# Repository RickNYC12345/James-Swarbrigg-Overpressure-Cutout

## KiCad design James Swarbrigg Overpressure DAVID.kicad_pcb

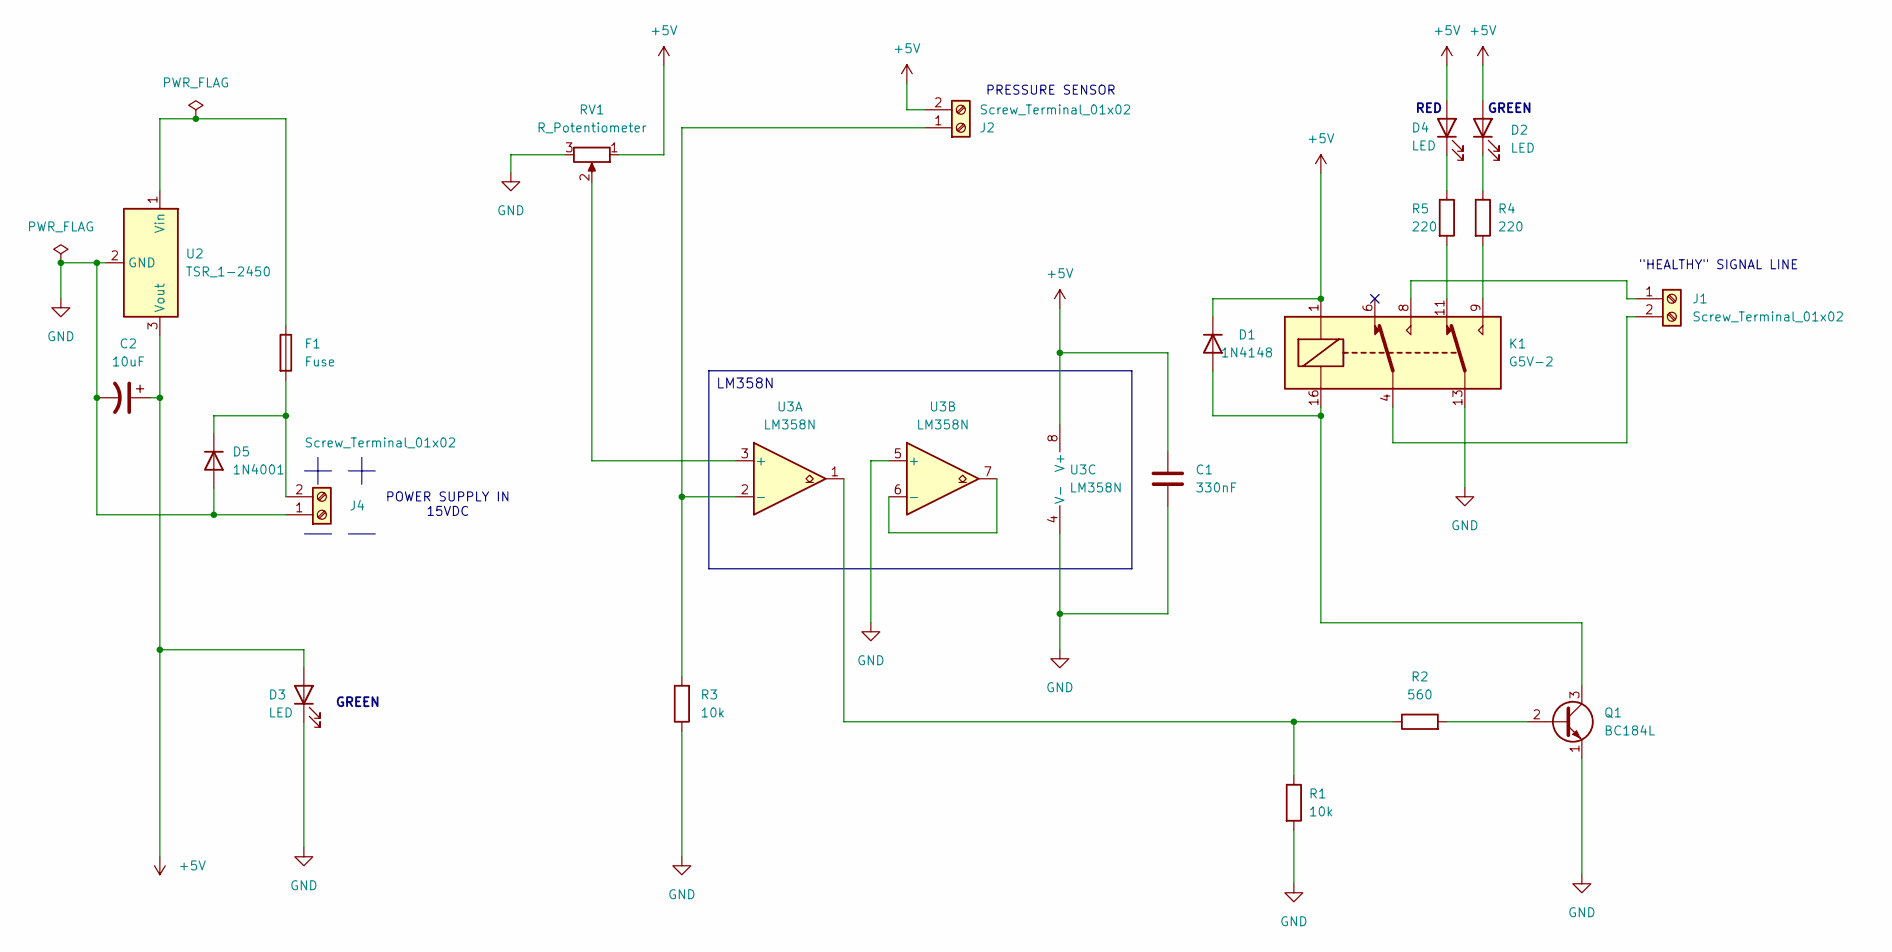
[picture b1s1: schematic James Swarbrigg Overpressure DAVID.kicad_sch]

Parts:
C1: 330nF; C_Rect_L7.2mm_W3.5mm_P5.00mm_FKS2_FKP2_MKS2_MKP2
C2: 10uF; CP_Radial_D5.0mm_P2.00mm
D1: 1N4148; D_DO-35_SOD27_P7.62mm_Horizontal
D2, D3, D4: LED; LED_D5.0mm
D5: 1N4001; D_DO-41_SOD81_P10.16mm_Horizontal
F1: Fuse; Fuseholder_Clip-5x20mm_Eaton_1A5601-01_Inline_P20.80x6.76mm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
J1, J2, J4: Screw_Terminal_01x02; TerminalBlock_Phoenix_MPT-0,5-2-2.54_1x02_P2.54mm_Horizontal
K1: G5V-2; Relay_DPDT_Omron_G5V-2
Q1: BC184L; TO-92_Inline
R1, R3: 10k; R_Axial_DIN0207_L6.3mm_D2.5mm_P10.16mm_Horizontal
R2: 560; R_Axial_DIN0207_L6.3mm_D2.5mm_P10.16mm_Horizontal
R4, R5: 220; R_Axial_DIN0207_L6.3mm_D2.5mm_P10.16mm_Horizontal
RV1: R_Potentiometer; Potentiometer_Bourns_3299P_Horizontal
U2: TSR_1-2450; Converter_DCDC_TRACO_TSR-1_THT
U3: LM358N; DIP-8_W7.62mm

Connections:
+5V: C1.1, C2.1, D1.1 (K), D2.2 (A), D3.2 (A), D4.2 (A), J2.2, K1.1, RV1.1, U2.3 (Vout), U3.8 (V+)
GND: C1.2, C2.2, D3.1 (K), D5.2 (A), J4.1, K1.13, Q1.1 (E), R1.2, R3.1, RV1.3, U2.2 (GND), U3.4 (V-), U3.5 (+)
unnamed: D1.2 (A), K1.16, Q1.3 (C)
unnamed: D2.1 (K), R4.1
unnamed: D4.1 (K), R5.1
unnamed: D5.1 (K), F1.2, J4.2
unnamed: J1.1, K1.8
unnamed: J1.2, K1.4
unnamed: J2.1, R3.2, U3.2 (-)
unnamed: K1.9, R4.2
unnamed: K1.11, R5.2
unnamed: Q1.2 (B), R2.2
unnamed: R1.1, R2.1, U3.1
unnamed: F1.1, U2.1 (Vin)
unnamed: RV1.2, U3.3 (+)
unnamed: U3.6 (-), U3.7

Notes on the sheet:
"HEALTHY" SIGNAL LINE
POWER SUPPLY IN 15VDC
GREEN
PRESSURE SENSOR
RED
LM358N

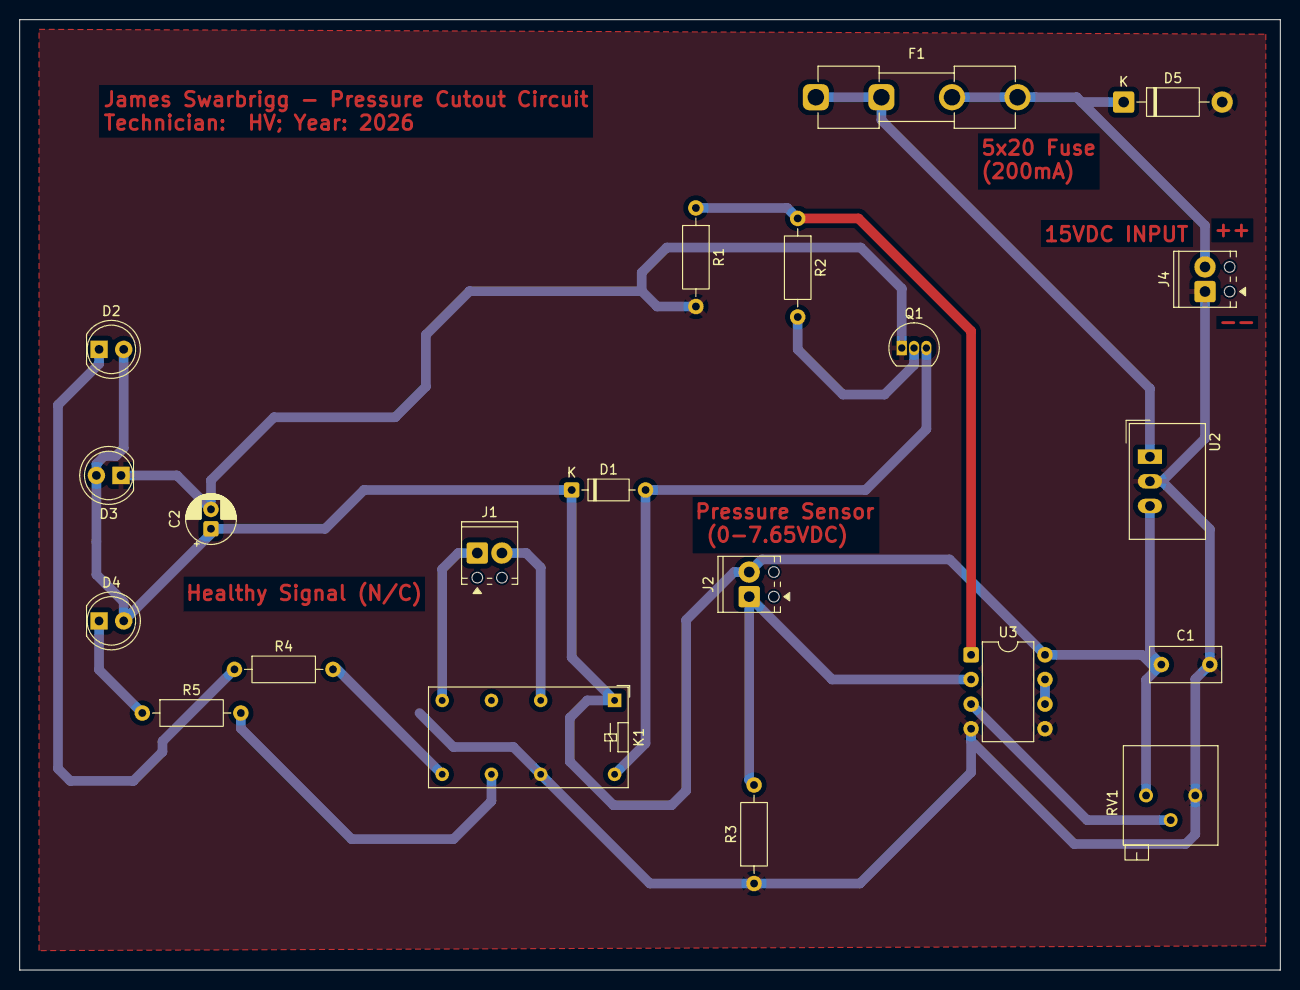
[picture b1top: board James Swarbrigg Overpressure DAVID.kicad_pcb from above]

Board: 2 copper layers, 130.0 x 98.0 mm, 21 parts (0 on the bottom side), 16 nets.

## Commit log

2026-06-26 Initial commit of James overpressure cutoout board
2026-06-30 Update overpressure cutout PCB and add Gerbers V1
2026-06-30 Ignore KiCad backup and cache files
